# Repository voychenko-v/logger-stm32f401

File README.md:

# Env Logger на STM32F401

Автономний логер параметрів середовища на **STM32F401CCU6**. Кожні *N* секунд система зчитує температуру, вологість і тиск (BME280), освітленість (фоторезистор GL5516) та час (DS3231), формує запис і асинхронно виводить його в UART-термінал. Збої шини I2C обробляються автоматично, а watchdog перезапускає систему, якщо вона зависне.

## Можливості

- Вимірювання T / H / P (BME280, I2C), мітка часу (DS3231, I2C), освітленість (GL5516, ADC1 + DMA)
- Інтервал опитування 1..3600 с, змінюється на ходу командою з терміналу
- Асинхронний вивід: кільцевий буфер + DMA (`printf` не блокує цикл)
- Консоль керування по UART RX (встановлення часу, інтервал, статус, скидання лічильника помилок)
- Відновлення після збоїв I2C: повтори, скидання шини, повторна ініціалізація датчиків
- Незалежний watchdog (IWDG) і журнал причини скидання
- Перевірка коректності даних і введення, захист від переповнення буферів

## Формат логу

```
[14:11:35] T:18.9 H:58.6 P:1004.5 LUX:19 ERR:0
```

| Поле | Значення |
|---|---|
| `[HH:MM:SS]` | час з DS3231 |
| `T` | температура, °C |
| `H` | відносна вологість, % |
| `P` | атмосферний тиск, гПа |
| `LUX` | освітленість, лк (`ERR`, якщо датчик відключений) |
| `ERR` | накопичений лічильник вичерпаних циклів помилок |

Службові повідомлення: `[WARN] retry N/3 ...`, `[ERR] ... bus recovery`, `Sensors: RTC OK, BME280 OK`, `Reset reason: ...`.

## Апаратна частина

| Компонент | Призначення |
|---|---|
| STM32F401CCU6 (Black Pill), кварц HSE 25 МГц | МК, 84 МГц |
| BME280 (I2C, 0x76) | температура, вологість, тиск |
| DS3231 (I2C, 0x68) | годинник реального часу |
| GL5516 + резистор 10 кОм | освітленість (дільник напруги) |
| USB-TTL адаптер CH340 | UART-термінал |
| Pull-up 10 кОм на SDA/SCL | підтяжка шини I2C |

Усі датчики живляться від **3.3 В**.

## Розпіновка

| Сигнал | Пін | Периферія |
|---|---|---|
| I2C SCL | PB6 | I2C1, 400 кГц |
| I2C SDA | PB7 | I2C1 |
| UART TX | PA2 | USART2, 115200 8N1, DMA |
| UART RX | PA3 | USART2, переривання |
| Фоторезистор | PA1 | ADC1_IN1, DMA circular |
| Відлагодження | PA13, PA14 | SWDIO, SWCLK |

## Архітектура

Суперцикл (без RTOS) на основі станів і переривань. Код розділений на три шари:

| Шар | Модулі | Відповідальність |
|---|---|---|
| Periph | `uart_log`, `uart_rx`, `i2c_bus`, `ds3231`, `bme280`, `light` | робота з периферією та датчиками |
| Logic | `logger`, `log_entry`, `log_format`, `cli` | рішення: коли міряти, що записати, як реагувати на команду |
| Reliability | `watchdog`, `reset_info`, відновлення в `logger` і `i2c_bus` | захист від збоїв |

Залежності ідуть лише вниз: драйвери нічого не знають про логер.

### Чому не RTOS

Система виконує одну періодичну задачу (опитування раз на секунди) і консоль із низьким навантаженням. Весь доступ до I2C здійснюється з одного контексту (основний цикл), а спільні дані між ISR і циклом це 32-бітні прапори та лічильники й кільцеві буфери з одним виробником і одним споживачем. Тому гонки виключені за побудовою, і ні мьютекси, ні черги не потрібні. Додавання RTOS збільшило б обсяг пам'яті та складність без виграшу в надійності.

### Принципи

- **Переривання лише виставляють прапор або кладуть байт у буфер**, уся логіка в основному циклі.
- **Жодного блокуючого очікування в штатному циклі:** очікування конвертації BME280 реалізоване станом `CONVERTING`, а не `delay()`.
- **Кільцеві буфери «один пише, один читає»** (`head` змінює лише виробник, `tail` лише споживач), тому блокування не потрібні.
- Усі виклики HAL I2C мають тайм-аут, а помилки повертаються як `status_t` і не ігноруються.

## Використані інтерфейси

| Інтерфейс | Навіщо | Нюанси реалізації |
|---|---|---|
| **I2C1** (400 кГц) | BME280, DS3231 на спільній шині | зовнішні pull-up, адреси 0x76 і 0x68, відновлення зависшої шини |
| **USART2 TX + DMA** | вивід логу | кільцевий буфер 1 КБ, завершення передачі по перериванню |
| **USART2 RX + IT** | консоль | буфер 128 Б, обробка помилок overrun |
| **ADC1 + DMA (circular)** | фоторезистор | 16 відліків, середнє; тривалість вибірки 480 тактів |
| **TIM3 + IRQ** | тік опитування | 1 с (PSC 8399, ARR 9999), інтервал рахується програмно |
| **IWDG** | захист від зависання | тайм-аут ≈4 с, тактування від LSI |

## Консоль керування

Підключення: 115200 8N1, закінчення рядка `Enter`. Локальне ехо в терміналі вимкнути (ехо повертає плата).

| Команда | Дія |
|---|---|
| `help` | список команд |
| `time` | поточний час RTC |
| `settime YYYY-MM-DD HH:MM:SS` | встановити час |
| `interval N` | інтервал опитування, `N` = 1..3600 с |
| `errclr` | скинути лічильник помилок |
| `status` | інтервал, лічильники помилок, втрат TX і переповнень RX |

Некоректні команди й аргументи відхиляються з повідомленням `ERR: ...`, система не зависає.

## Стратегія обробки помилок

| Ситуація | Реакція |
|---|---|
| Збій читання датчика (NACK, тайм-аут, дані поза межами) | до 3 спроб із паузою 100 мс без блокування (`[WARN] retry`) |
| Три невдачі поспіль | `ERR`++, відновлення шини (до 9 імпульсів SCL + STOP), повторна ініціалізація датчиків |
| Датчик відсутній при старті | система стартує, при кожному циклі повторює ініціалізацію |
| Фоторезистор відключений або замкнений | `LUX:ERR`, решта запису нормальна, I2C не чіпається |
| Годинник втратив живлення (прапор OSF) | запис часу компіляції при старті, виправляється `settime` |
| Переповнення TX-буфера | повідомлення відкидається, лічильник `tx dropped` у `status` |
| Переповнення RX-буфера, рядок надто довгий | байти відкидаються, `ERR: line too long` |
| Зависання програми | IWDG через ≈4 с скидає МК, у логу `Reset reason: IWDG (watchdog)` |

Валідація: тиск 300–1100 гПа, вологість 0–100 %, температура від -40 до 85 °C, дані «вимірювання не відбулося» (`0x80000` / `0x8000`) відкидаються; АЦП поза межами 5..4090 вважається несправністю датчика.

### Важливі налаштування CubeMX

- HSE 25 МГц, PLL до 84 МГц; Debug = Serial Wire
- USART2: **ввімкнути `USART2 global interrupt`** (без нього DMA-передача зупиняється після першого шматка)
- ADC1: Continuous Conversion і DMA Continuous Requests увімкнено, DMA в режимі Circular
- Для виведення `float` у `printf` увімкнути *Use float with printf from newlib-nano*
- Для налагодження IWDG заморожується відладчиком (`__HAL_DBGMCU_FREEZE_IWDG()`)

## Продуктивність

- **DMA:** передача логу в UART і опитування АЦП фоторезистора виконуються DMA без участі процесора.
- **Копіювання даних:** запис потрапляє в кільцевий буфер TX один раз, далі DMA читає з нього безпосередньо в UART.
- **I2C:** читання BME280 і DS3231 (близько 15 байтів раз на кілька секунд) виконується блокуючими викликами HAL із тайм-аутом 10–20 мс. Використання DMA тут не виправдане: обсяг даних малий, а складність зросла б.

## Тестування і демонстрація

| Сценарій | Очікуваний результат |
|---|---|
| Штатна робота понад 5 хвилин | рядки з заданим інтервалом, `ERR:0` |
| Відключення BME280 на ходу | `[WARN] retry`, `[ERR] ... bus recovery`, після підключення дані повертаються без перезавантаження |
| Відключення DS3231 | те саме для RTC |
| Відключення фоторезистора | `LUX:ERR`, решта запису нормальна |
| Некоректні команди (`interval 0`, `interval abc`, `settime foo`, дуже довгий рядок) | `ERR: ...`, система не зависає |
| Імітація зависання (`WDT_TEST_HANG`) | близько 4 с тиші, перезапуск, `Reset reason: IWDG (watchdog)` |

```
[WARN] retry 1/3 rtc=4 bme=0
[WARN] retry 2/3 rtc=4 bme=0
[ERR] rtc=4 bme=0 ERR:6, bus recovery
Sensors: RTC OK, BME280 OK
[12:08:40] T:19.1 H:45.9 P:985.8 LUX:1 ERR:6
```

## PCB

Проєкт власної двошарової плати розміром 60x45 мм у KiCad: ті самі функції, що й прототип, але з окремих мікросхем замість модулів. ERC і DRC пройдено без помилок. Вихідні файли проєкту лежать у [hardware/env-logger/](hardware/env-logger/)

| Файл | Вміст |
|---|---|
| [`hardware/shematic.pdf`](hardware/shematic.pdf) | принципова схема |
| [`hardware/env-logger.csv`](hardware/env-logger.csv) | специфікація (BOM) |
| `hardware/*.kicad_sch`, `*.kicad_pcb` | вихідні файли проєкту |
 
### Склад плати
 
| Блок | Компоненти |
|---|---|
| Живлення | USB-C (лише 5 В, резистори 5,1 кОм на лініях CC), стабілізатор AP2112K-3.3, конденсатори 1 мкФ X7R на вході й виході, світлодіод живлення |
| Мікроконтролер | STM32F401CCU6 (UFQFPN48), кварц 25 МГц із конденсаторами 15 пФ, кнопки NRST і BOOT0, роз'єм SWD |
| Датчики | BME280 (LGA-8, I2C 0x76), DS3231MZ (SOIC-8, I2C 0x68) з батарейкою CR2032 |
| Шина I2C | підтяжки 4,7 кОм на SDA і SCL |
| Освітленість | GL5516 на платі, дільник із резистором 10 кОм, конденсатор 100 нФ на вході АЦП |
| Інтерфейси | роз'єм UART (GND, TX, RX), роз'єм SWD (3V3, SWDIO, SWCLK, GND, NRST) |
| Налагодження | 10 тест-поінтів: `+5V`, `+3V3`, `GND` ×2, `SDA`, `SCL`, `UART_TX`, `UART_RX`, `ADC_LDR`, `NRST` |
 
### Ключові рішення
 
- **Розв'язка живлення.** Окремий конденсатор 100 нФ на кожному виводі VDD мікроконтролера, розміщений поруч із виводом. VBAT з'єднано з `+3V3`, власний годинник МК не використовується, час веде DS3231.
- **Живлення ядра.** На виводі VCAP1 стоїть керамічний конденсатор 2,2 мкФ (вимога МК до внутрішнього регулятора). Для корпусу UFQFPN48 потрібен лише один такий конденсатор.
- **Аналогове живлення.** Вивід VDDA/VREF+ підключено до `+3V3` через феритову бусину з конденсаторами 100 нФ і 1 мкФ.
- **Розділення силової та логічної частин.** Вхід USB-C, стабілізатор і індикатор живлення зібрані в окремій зоні плати, відокремленій від мікроконтролера й датчиків.
- **Швидкі сигнали.** Високошвидкісних інтерфейсів у проєкті немає (USB працює лише як джерело живлення, лінії D+ та D- не використовуються). Найвищі частоти це кварц 25 МГц і I2C 400 кГц. Кварц із конденсаторами розміщено впритул до виводів PH0 і PH1, доріжки короткі, поруч чужих сигналів немає.
- **Підтяжки I2C.** На платі використано 4,7 кОм замість 10 кОм з прототипу: це дає запас по часу наростання сигналу на 400 кГц.
- **Тепловий режим.** BME280 розташовано далеко від стабілізатора й мікроконтролера, щоб їхнє тепло не спотворювало вимірювання температури. Фоторезистор винесено на край плати подалі від світлодіода живлення.
- **Захист від помилкового режиму.** Виводи BOOT0 і BOOT1 (PB2) підтягнуто до землі, тому плата стартує з флеш-пам'яті; вхід у завантажувач виконується кнопкою.
- **Тест-поінти** виведені на ключові лінії живлення й сигналів і підписані на шовкографії.

### Відмінності від прототипу
 
| | Прототип | PCB |
|---|---|---|
| Мікроконтролер | плата Black Pill | чіп STM32F401CCU6 на платі |
| Годинник | DS3231SN (±2 ppm, модуль) | DS3231MZ (±5 ppm) |
| Підтяжки I2C | 10 кОм | 4,7 кОм |
| Живлення | через Black Pill, датчики від 3,3 В | USB-C + стабілізатор 3,3 В |
| Підключення програматора | роз'єм плати | роз'єм SWD на платі |

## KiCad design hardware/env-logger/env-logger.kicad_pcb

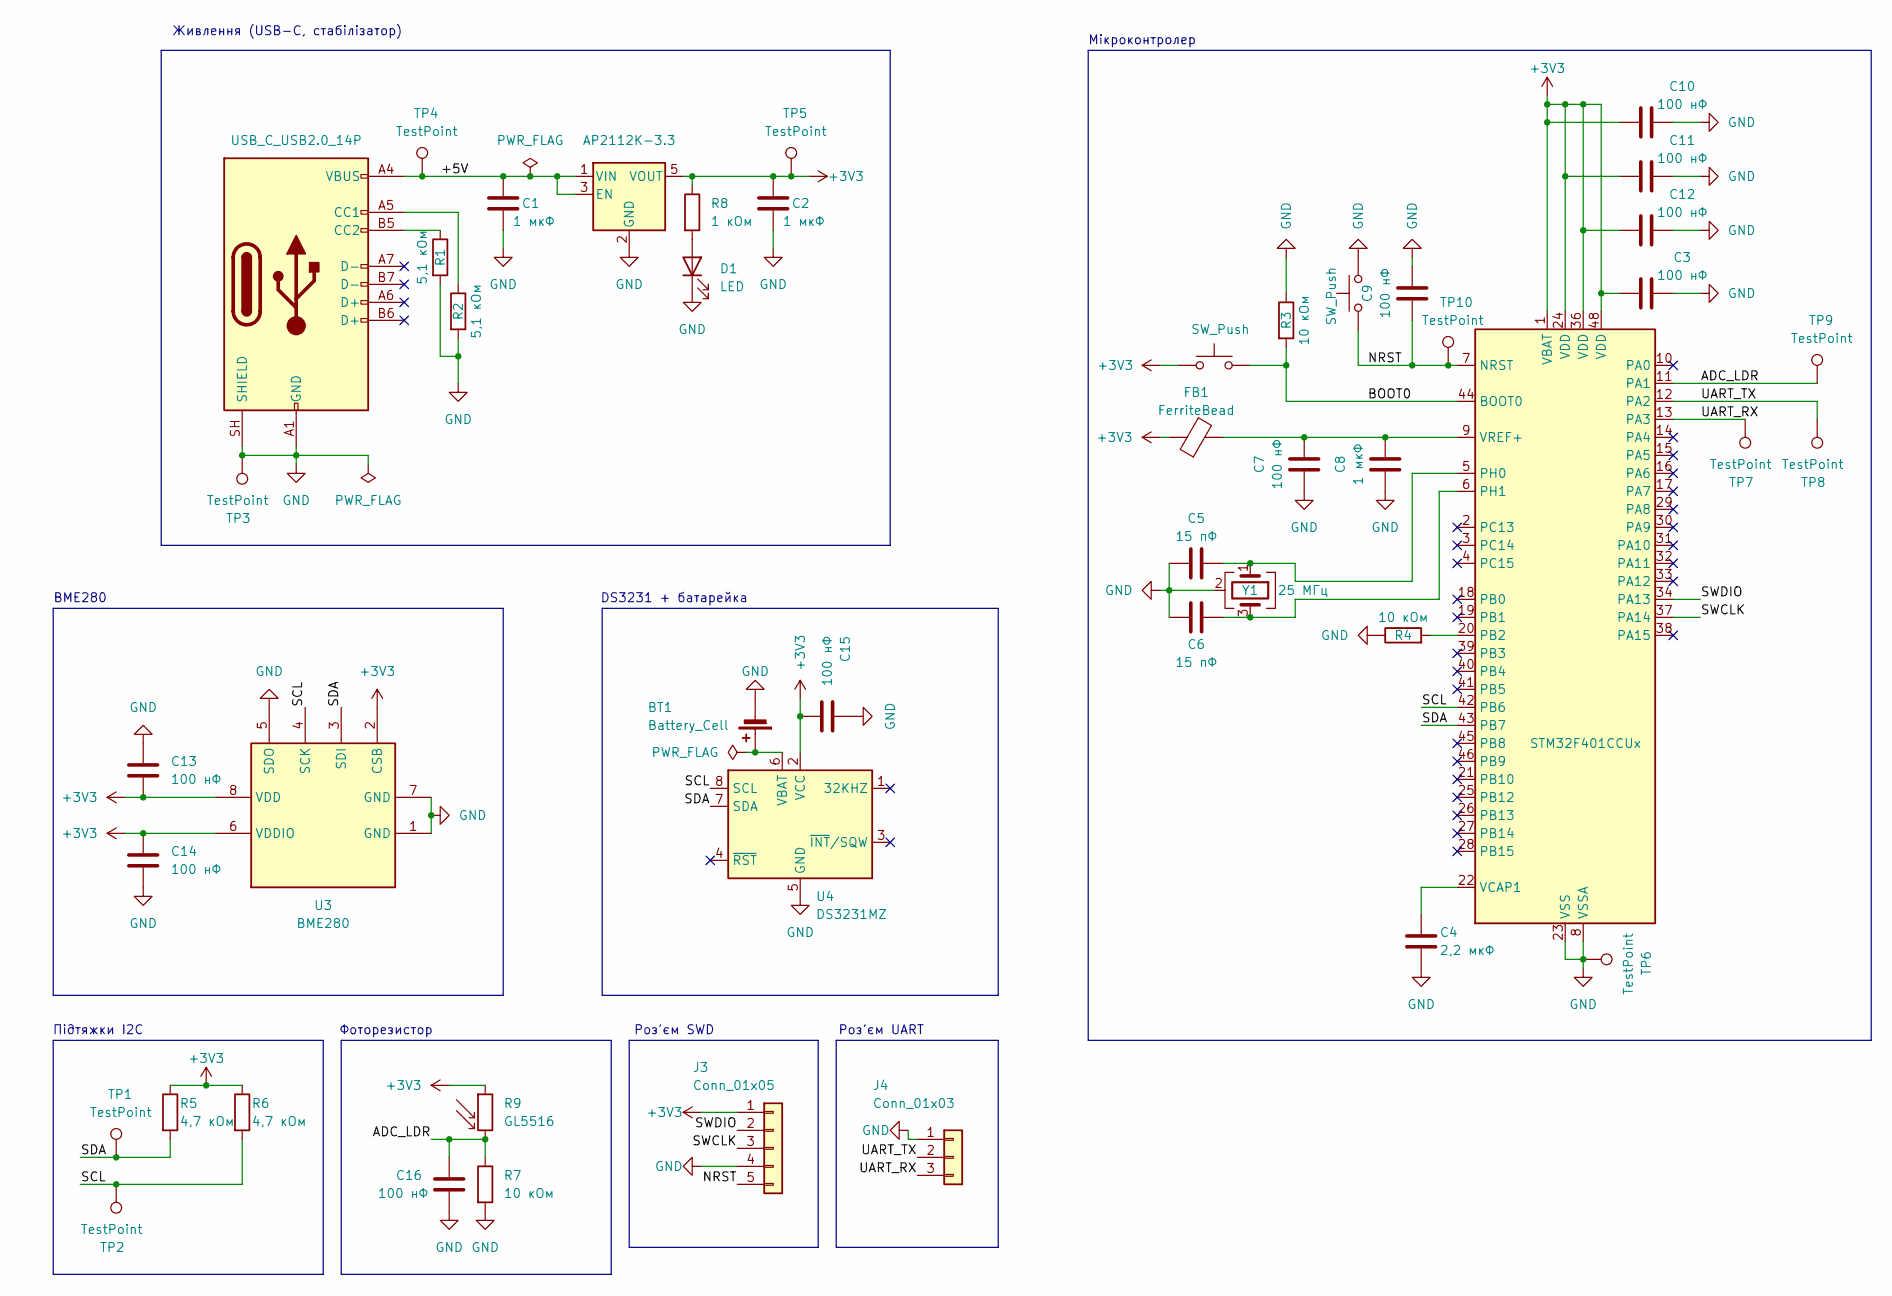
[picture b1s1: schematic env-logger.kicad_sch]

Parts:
BT1: Battery_Cell; BatteryHolder_Keystone_3034_1x20mm
C1, C2, C8: 1 мкФ; C_0603_1608Metric
C3, C7, C9, C10, C11, C12, C13, C14, C15, C16: 100 нФ; C_0603_1608Metric
C4: 2,2 мкФ; C_0603_1608Metric
C5, C6: 15 пФ; C_0603_1608Metric
D1: LED; LED_0603_1608Metric
FB1: FerriteBead; L_0603_1608Metric
J1: USB_C_USB2.0_14P; USB_C_Receptacle_HRO_TYPE-C-31-M-12
J3: Conn_01x05; PinHeader_1x05_P2.54mm_Vertical
J4: Conn_01x03; PinHeader_1x03_P2.54mm_Vertical
R1, R2: 5,1 кОм; R_0603_1608Metric
R3, R4, R7: 10 кОм; R_0603_1608Metric
R5, R6: 4,7 кОм; R_0603_1608Metric
R8: 1 кОм; R_0603_1608Metric
R9: GL5516; R_LDR_5.0x4.1mm_P3mm_Vertical
SW1, SW2: SW_Push; SW_SPST_PTS645Sx43SMTR92
TP1, TP2, TP3, TP4, TP5, TP6, TP7, TP8, TP9, TP10: TestPoint; TestPoint_Pad_D1.5mm
U1: AP2112K-3.3; SOT-23-5
U2: STM32F401CCUx; QFN-48-1EP_7x7mm_P0.5mm_EP5.6x5.6mm
U3: BME280; Bosch_LGA-8_2.5x2.5mm_P0.65mm_ClockwisePinNumbering
U4: DS3231MZ; SOIC-8_3.9x4.9mm_P1.27mm
Y1: 25 МГц; Crystal_SMD_3225-4Pin_3.2x2.5mm

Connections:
+3V3: C2.1, C3.1, C10.1, C11.1, C12.1, C13.2, C14.1, C15.2, FB1.1, J3.1, R5.1, R6.1, R8.1, R9.1, SW1.1, TP5.1 (1_1), U1.5 (VOUT), U2.1 (VBAT), U2.24 (VDD), U2.36 (VDD), U2.48 (VDD), U3.2 (CSB), U3.6 (VDDIO), U3.8 (VDD), U4.2 (VCC)
/+5V: C1.1, J1.A4 (VBUS), J1.A9 (VBUS), J1.B4 (VBUS), J1.B9 (VBUS), TP4.1 (1_1), U1.1 (VIN), U1.3 (EN)
/ADC_LDR: C16.1, R7.1, R9.2, TP9.1 (1_1), U2.11 (PA1)
/BOOT0: R3.2, SW1.2, U2.44 (BOOT0)
/NRST: C9.1, J3.5, SW2.1, TP10.1 (1_1), U2.7 (NRST)
/SCL: R6.2, TP2.1 (1_1), U2.42 (PB6), U3.4 (SCK), U4.8 (SCL)
/SDA: R5.2, TP1.1 (1_1), U2.43 (PB7), U3.3 (SDI), U4.7 (SDA)
/SWCLK: J3.3, U2.37 (PA14)
/SWDIO: J3.2, U2.34 (PA13)
/UART_RX: J4.3, TP7.1 (1_1), U2.13 (PA3)
/UART_TX: J4.2, TP8.1 (1_1), U2.12 (PA2)
GND: BT1.2 (-), C1.2, C2.2, C3.2, C4.2, C5.2, C6.2, C7.2, C8.2, C9.2, C10.2, C11.2, C12.2, C13.1, C14.2, C15.1, C16.2, D1.1 (K), J1.A1 (GND), J1.A12 (GND), J1.B1 (GND), J1.B12 (GND), J1.SH (SHIELD), J3.4, J4.1, R1.2, R2.2, R3.1, R4.1, R7.2, SW2.2, TP3.1 (1_1), TP6.1 (1_1), U1.2 (GND), U2.8 (VSSA), U2.23 (VSS), U2.35 (VSS), U2.47 (VSS), U2.49 (VSS), U3.1 (GND), U3.5 (SDO), U3.7 (GND), U4.5 (GND), Y1.2 (G), Y1.4 (G)
unnamed: BT1.1 (+), U4.6 (VBAT)
unnamed: D1.2 (A), R8.2
unnamed: J1.A5 (CC1), R2.1
unnamed: J1.B5 (CC2), R1.1
unnamed: R4.2, U2.20 (PB2)
unnamed: C5.1, U2.5 (PH0), Y1.1
unnamed: C6.1, U2.6 (PH1), Y1.3
unnamed: C4.1, U2.22 (VCAP1)
unnamed: C7.1, C8.1, FB1.2, U2.9 (VREF+)

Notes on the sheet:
Живлення (USB-C, стабілізатор)
Мікроконтролер
Роз'єм UART
DS3231 + батарейка
Роз'єм SWD
Підтяжки I2C
Фоторезистор
BME280

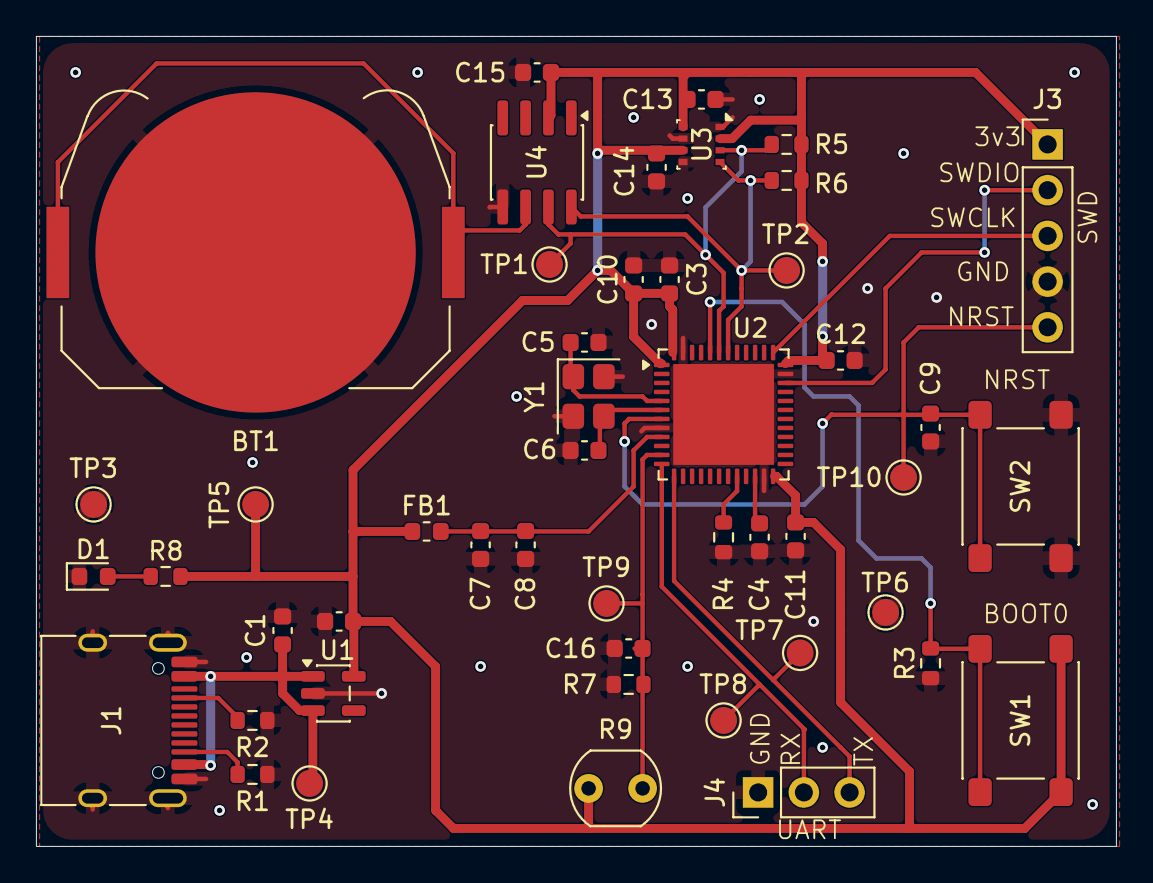
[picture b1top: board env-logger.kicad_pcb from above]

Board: 2 copper layers, 60.0 x 45.0 mm, 48 parts (0 on the bottom side), 21 nets.

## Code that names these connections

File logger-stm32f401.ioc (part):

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Mcu.Name=STM32F401C(B-C)Ux
Mcu.Package=UFQFPN48
Mcu.UserName=STM32F401CCUx
PA1.Signal=ADCx_IN1
PA13.Mode=Serial_Wire
PA13.Signal=SYS_JTMS-SWDIO
PA14.Mode=Serial_Wire
PA14.Signal=SYS_JTCK-SWCLK
PA2.Mode=Asynchronous
PA2.Signal=USART2_TX
PA3.Mode=Asynchronous
PA3.Signal=USART2_RX
PB6.Mode=I2C
PB6.Signal=I2C1_SCL
PB7.Mode=I2C
PB7.Signal=I2C1_SDA
PH0\ -\ OSC_IN.Mode=HSE-External-Oscillator
PH0\ -\ OSC_IN.Signal=RCC_OSC_IN
PH1\ -\ OSC_OUT.Mode=HSE-External-Oscillator
PH1\ -\ OSC_OUT.Signal=RCC_OSC_OUT
RCC.HSE_VALUE=25000000
RCC.SYSCLKFreq_VALUE=84000000
RCC.SYSCLKSource=RCC_SYSCLKSOURCE_PLLCLK
board=custom
